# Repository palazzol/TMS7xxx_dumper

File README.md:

# Internal ROM dumper for TMS7xxx series chips

Texas Instruments made a series of chips based on the TMS7000 microprocessor, which can contain internal programs in mask ROM.
General Instrument / Microchip made versions of these chips as well (PIC7000 series).

In addition, at least one commercial IC with a different label is actually one of these internally.
For example, the CTS256A-AL2, which was sold at Radio Shack, is actually a PIC7041.

This design supports all known chips in the series, including:
PIC70XX, TMS70XX, TMS70XXX, TMS77XX, TMS70CXX, and TMS77CXX

This project uses some external code to dump the normally hidden mask ROM, and feed it to a host PC.
In addition, it can identify the type of chip by determining the following parameters:
- RAM size
- ROM size
- Presence of Serial Port
- Process (NMOS or CMOS)

# Instructions:

- Program a 4K 2732-compatible EPROM or FLASH chip with the dumper.bin (Trojan program)
- Program the Arduino Nano with the sketch dumper7k.ino
- Connect via serial terminal, baud rate 115200, 8N1.
- Follow the instructions on screen to identify the chip type and dump any internal rom as a Motorola S-Record format file to the screen
- Save S-Record lines to a .s19 file
- Convert file to binary using srec_cat, or similar tool:

`srec_cat -o <filename>.bin -Binary <filename>.s19`

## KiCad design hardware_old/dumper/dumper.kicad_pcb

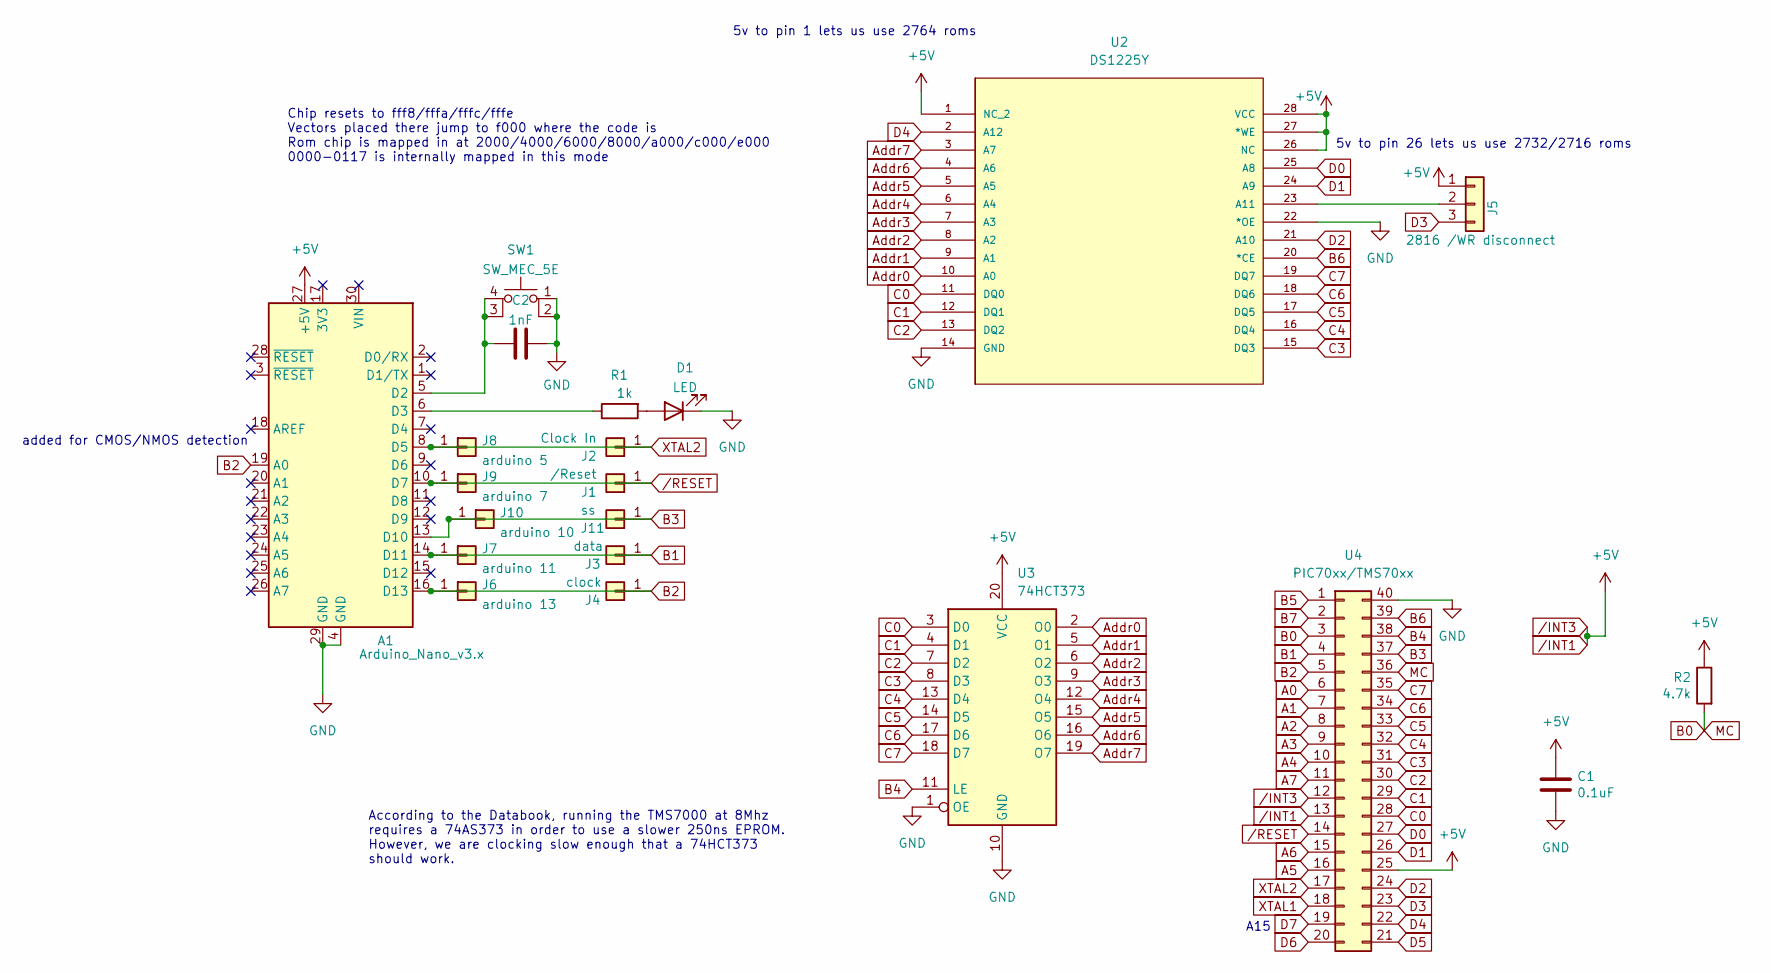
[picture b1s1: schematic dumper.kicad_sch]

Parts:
A1: Arduino_Nano_v3.x; Arduino_Nano
C1: 0.1uF; C_Axial_L3.8mm_D2.6mm_P7.50mm_Horizontal
C2: 1nF; C_Axial_L3.8mm_D2.6mm_P7.50mm_Horizontal
D1: LED; LED_D5.0mm
J1: /Reset; PinHeader_1x01_P2.54mm_Vertical
J2: Clock In; PinHeader_1x01_P2.54mm_Vertical
J3: data; PinHeader_1x01_P2.54mm_Vertical
J4: clock; PinHeader_1x01_P2.54mm_Vertical
J5: 2816 /WR disconnect; PinHeader_1x03_P2.54mm_Vertical
J6: arduino 13; PinHeader_1x01_P2.54mm_Vertical
J7: arduino 11; PinHeader_1x01_P2.54mm_Vertical
J8: arduino 5; PinHeader_1x01_P2.54mm_Vertical
J9: arduino 7; PinHeader_1x01_P2.54mm_Vertical
J10: arduino 10; PinHeader_1x01_P2.54mm_Vertical
J11: ss; PinHeader_1x01_P2.54mm_Vertical
R1: 1k; R_Axial_DIN0207_L6.3mm_D2.5mm_P2.54mm_Vertical
R2: 4.7k; R_Axial_DIN0207_L6.3mm_D2.5mm_P2.54mm_Vertical
SW1: SW_MEC_5E; SW_TH_Tactile_Omron_B3F-10xx
U2: DS1225Y; 21-0245A_28; MANUFACTURER_PART_NUMBER DS1225Y150+
U3: 74HCT373; DIP-20_W7.62mm
U4: PIC70xx/TMS70xx; DIP-40_W15.24mm

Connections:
A0: U4.6
A1: U4.7
A2: U4.8
A3: U4.9
A4: U4.10
A5: U4.16
A6: U4.15
A7: U4.11
Addr0: U2.10 (A0), U3.2 (O0)
Addr1: U2.9 (A1), U3.5 (O1)
Addr2: U2.8 (A2), U3.6 (O2)
Addr3: U2.7 (A3), U3.9 (O3)
Addr4: U2.6 (A4), U3.12 (O4)
Addr5: U2.5 (A5), U3.15 (O5)
Addr6: U2.4 (A6), U3.16 (O6)
Addr7: U2.3 (A7), U3.19 (O7)
B0: R2.2, U4.3, U4.36
B1: A1.14 (D11), J3.1, J7.1, U4.4
B2: A1.16 (D13), A1.19 (A0), J4.1, J6.1, U4.5
B3: A1.13 (D10), J10.1, J11.1, U4.37
B4: U3.11 (LE), U4.38
B5: U4.1
B6: U2.20 (*CE), U4.39
B7: U4.2
C0: U2.11 (DQ0), U3.3 (D0), U4.28
C1: U2.12 (DQ1), U3.4 (D1), U4.29
C2: U2.13 (DQ2), U3.7 (D2), U4.30
C3: U2.15 (DQ3), U3.8 (D3), U4.31
C4: U2.16 (DQ4), U3.13 (D4), U4.32
C5: U2.17 (DQ5), U3.14 (D5), U4.33
C6: U2.18 (DQ6), U3.17 (D6), U4.34
C7: U2.19 (DQ7), U3.18 (D7), U4.35
D0: U2.25 (A8), U4.27
D1: U2.24 (A9), U4.26
D2: U2.21 (A10), U4.24
D3: J5.3, U4.23
D4: U2.2 (A12), U4.22
D5: U4.21
D6: U4.20
D7: U4.19
GND: A1.4 (GND), A1.29 (GND), C1.2, C2.1, D1.1 (K), SW1.1, SW1.2, U2.14 (GND), U2.22 (*OE), U3.1 (OE), U3.10 (GND), U4.40
unnamed: A1.5 (D2), C2.2, SW1.3 (K), SW1.4 (A)
unnamed: A1.6 (D3), R1.1
unnamed: D1.2 (A), R1.2
unnamed: J5.2, U2.23 (A11)
XTAL1: U4.18
XTAL2: A1.8 (D5), J2.1, J8.1, U4.17
/INT1: A1.27 (+5V), C1.1, J5.1, R2.1, U2.1 (NC_2), U2.26 (NC), U2.27 (*WE), U2.28 (VCC), U3.20 (VCC), U4.12, U4.13, U4.25
/RESET: A1.10 (D7), J1.1, J9.1, U4.14

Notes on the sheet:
According to the Databook, running the TMS7000 at 8Mhz requires a 74AS373 in order to use a slower 250ns EPROM. However, we are clocking slow enough that a 74HCT373 should work.
added for CMOS/NMOS detection
5v to pin 26 lets us use 2732/2716 roms
5v to pin 1 lets us use 2764 roms
Chip resets to fff8/fffa/fffc/fffe Vectors placed there jump to f000 where the code is Rom chip is mapped in at 2000/4000/6000/8000/a000/c000/e000 0000-0117 is internally mapped in this mode
A15

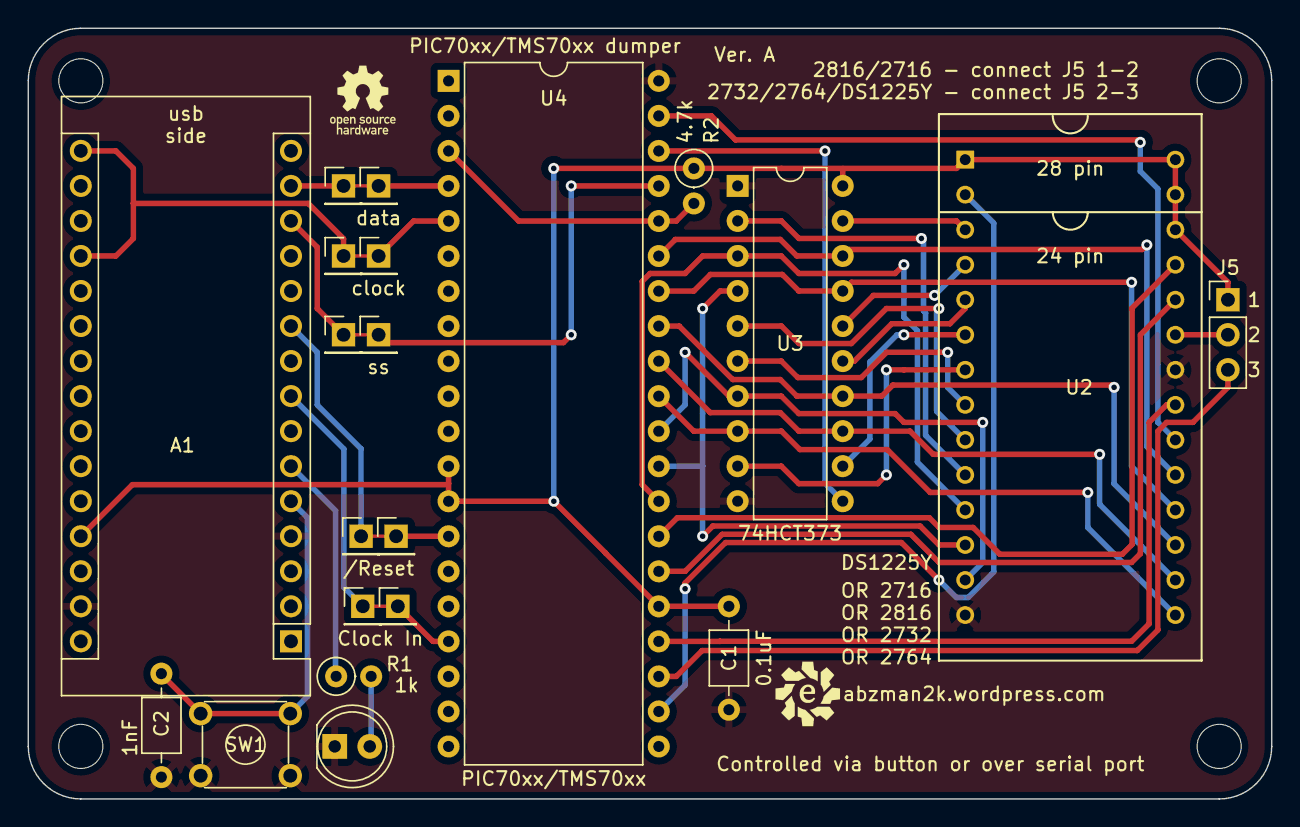
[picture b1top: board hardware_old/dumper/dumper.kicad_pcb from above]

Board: 2 copper layers, 90.2 x 55.9 mm, 21 parts (0 on the bottom side), 35 nets.

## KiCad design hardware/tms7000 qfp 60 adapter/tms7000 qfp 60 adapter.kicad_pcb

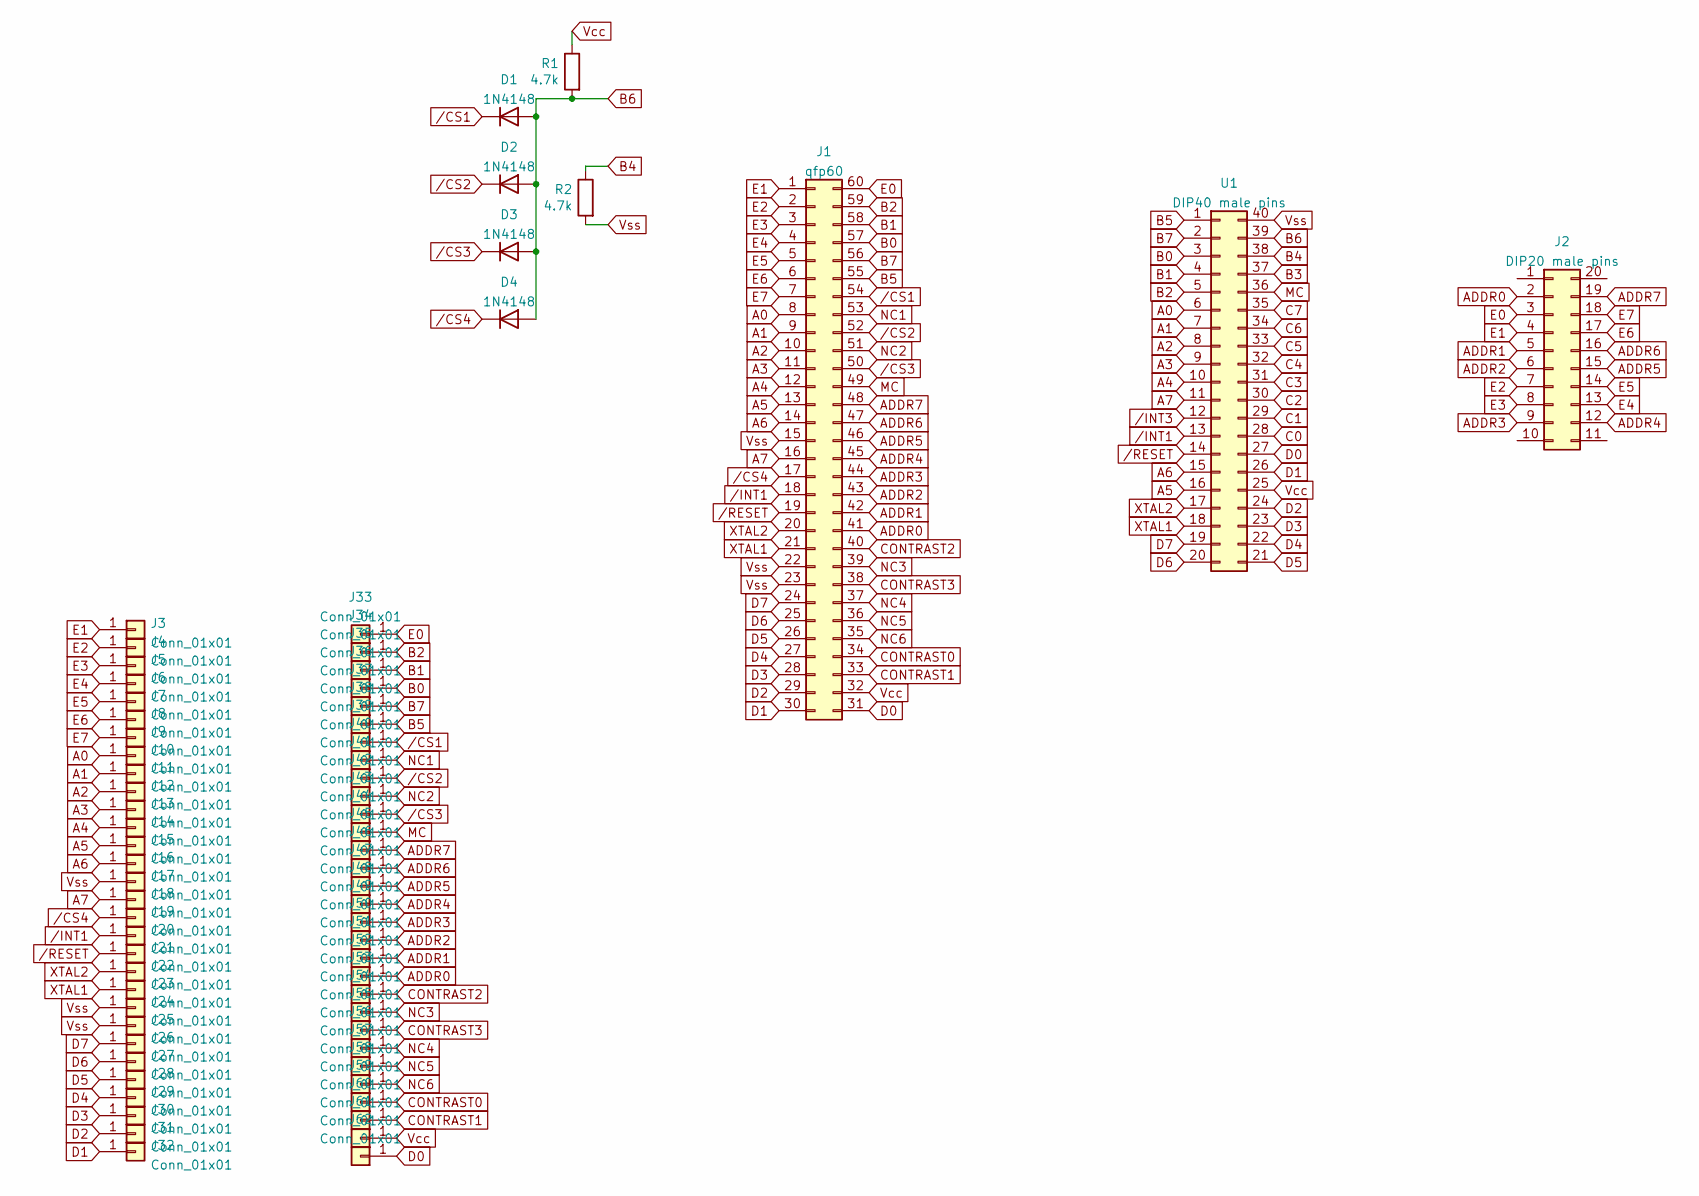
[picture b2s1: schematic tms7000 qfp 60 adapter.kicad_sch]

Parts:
D1, D2, D3, D4: 1N4148; D_DO-35_SOD27_P2.54mm_Vertical_AnodeUp
J1: qfp60; MQFP-60_P0.8mm
J2: DIP20 male pins; DIP-20_W7.62mm
J3, J4, J5, J6, J7, J8, J9, J10, J11, J12, J13, J14, J15, J16, J17, J18, J19, J20, J21, J22, J23, J24, J25, J26, J27, J28, J29, J30, J31, J32, J33, J34, J35, J36, J37, J38, J39, J40, J41, J42, J43, J44, J45, J46, J47, J48, J49, J50, J51, J52, J53, J54, J55, J56, J57, J58, J59, J60, J61, J62: Conn_01x01; PinHeader_1x01_P2.54mm_Vertical
R1, R2: 4.7k; R_Axial_DIN0207_L6.3mm_D2.5mm_P2.54mm_Vertical
U1: DIP40 male pins; DIP-40_W15.24mm

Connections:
A0: J1.8, J10.1, U1.6
A1: J1.9, J11.1, U1.7
A2: J1.10, J12.1, U1.8
A3: J1.11, J13.1, U1.9
A4: J1.12, J14.1, U1.10
A5: J1.13, J15.1, U1.16
A6: J1.14, J16.1, U1.15
A7: J1.16, J18.1, U1.11
ADDR0: J1.41, J2.2, J52.1
ADDR1: J1.42, J2.5, J51.1
ADDR2: J1.43, J2.6, J50.1
ADDR3: J1.44, J2.9, J49.1
ADDR4: J1.45, J2.12, J48.1
ADDR5: J1.46, J2.15, J47.1
ADDR6: J1.47, J2.16, J46.1
ADDR7: J1.48, J2.19, J45.1
B0: J1.57, J36.1, U1.3
B1: J1.58, J35.1, U1.4
B2: J1.59, J34.1, U1.5
B3: U1.37
B4: R2.1, U1.38
B5: J1.55, J38.1, U1.1
B6: D1.2 (A), D2.2 (A), D3.2 (A), D4.2 (A), R1.2, U1.39
B7: J1.56, J37.1, U1.2
C0: U1.28
C1: U1.29
C2: U1.30
C3: U1.31
C4: U1.32
C5: U1.33
C6: U1.34
C7: U1.35
CONTRAST0: J1.34, J59.1
CONTRAST1: J1.33, J60.1
CONTRAST2: J1.40, J53.1
CONTRAST3: J1.38, J55.1
D0: J1.31, J62.1, U1.27
D1: J1.30, J32.1, U1.26
D2: J1.29, J31.1, U1.24
D3: J1.28, J30.1, U1.23
D4: J1.27, J29.1, U1.22
D5: J1.26, J28.1, U1.21
D6: J1.25, J27.1, U1.20
D7: J1.24, J26.1, U1.19
E0: J1.60, J2.3, J33.1
E1: J1.1, J2.4, J3.1
E2: J1.2, J2.7, J4.1
E3: J1.3, J2.8, J5.1
E4: J1.4, J2.13, J6.1
E5: J1.5, J2.14, J7.1
E6: J1.6, J2.17, J8.1
E7: J1.7, J2.18, J9.1
MC: J1.49, J44.1, U1.36
NC1: J1.53, J40.1
NC2: J1.51, J42.1
NC3: J1.39, J54.1
NC4: J1.37, J56.1
NC5: J1.36, J57.1
NC6: J1.35, J58.1
Vcc: J1.32, J61.1, R1.1, U1.25
Vss: J1.15, J1.22, J1.23, J17.1, J24.1, J25.1, R2.2, U1.40
XTAL1: J1.21, J23.1, U1.18
XTAL2: J1.20, J22.1, U1.17
/CS1: D1.1 (K), J1.54, J39.1
/CS2: D2.1 (K), J1.52, J41.1
/CS3: D3.1 (K), J1.50, J43.1
/CS4: D4.1 (K), J1.17, J19.1
/INT1: J1.18, J20.1, U1.13
/INT3: U1.12
/RESET: J1.19, J21.1, U1.14

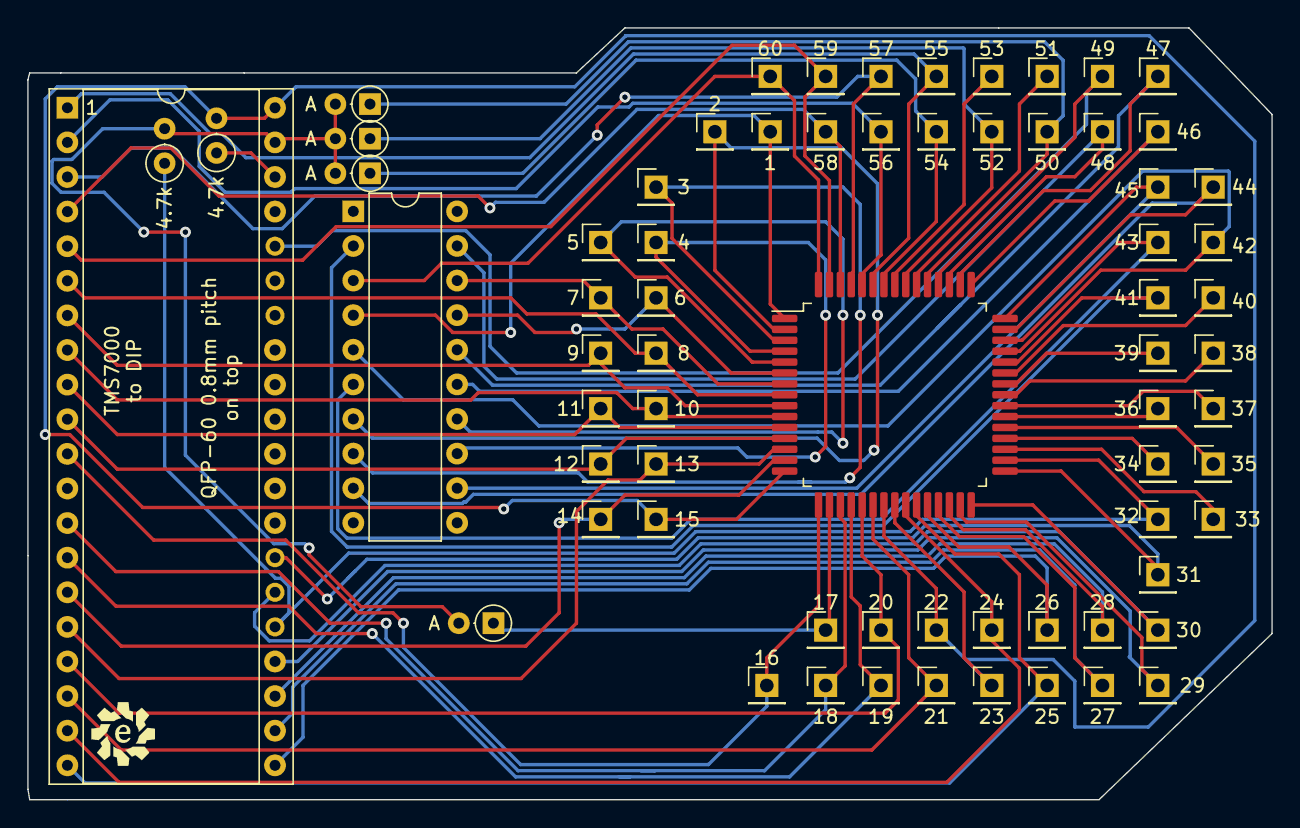
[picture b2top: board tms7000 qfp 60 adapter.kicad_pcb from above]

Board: 2 copper layers, 91.3 x 56.6 mm, 69 parts (0 on the bottom side), 60 nets.

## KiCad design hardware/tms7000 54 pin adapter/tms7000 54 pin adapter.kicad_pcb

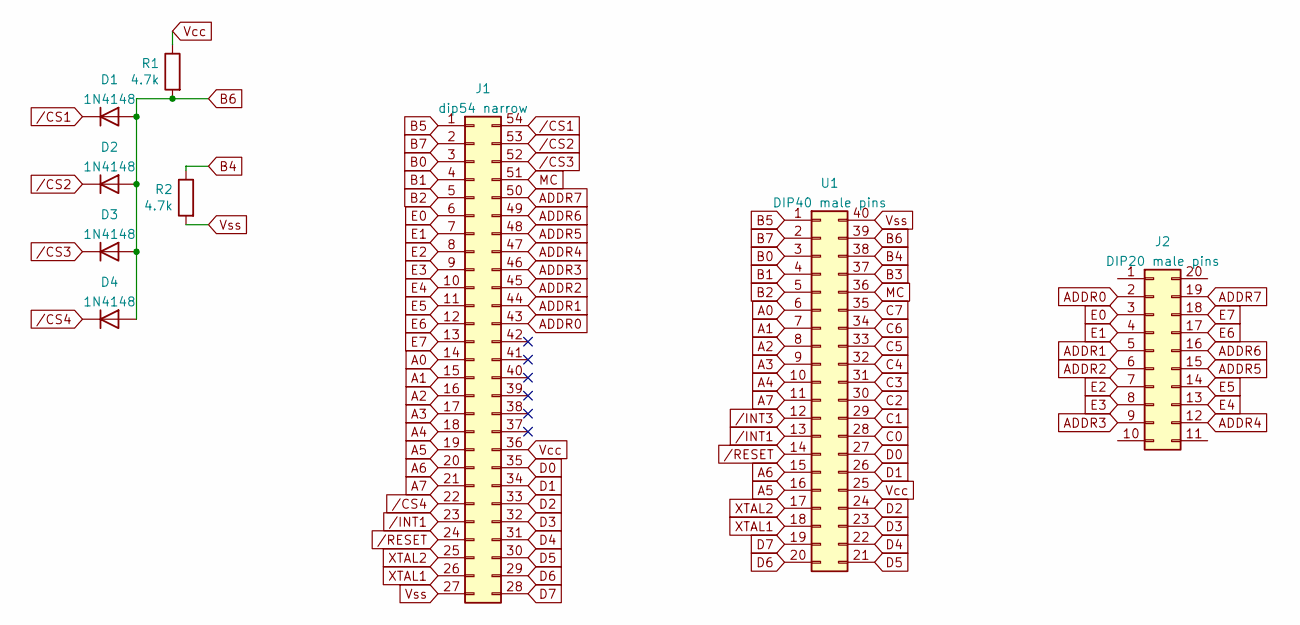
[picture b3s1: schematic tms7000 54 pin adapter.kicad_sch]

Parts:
D1, D2, D3, D4: 1N4148; D_DO-35_SOD27_P2.54mm_Vertical_AnodeUp
J1: dip54 narrow; DIP 54 1.78mm
J2: DIP20 male pins; DIP-20_W7.62mm
R1, R2: 4.7k; R_Axial_DIN0207_L6.3mm_D2.5mm_P2.54mm_Vertical
U1: DIP40 male pins; DIP-40_W15.24mm

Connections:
A0: J1.14, U1.6
A1: J1.15, U1.7
A2: J1.16, U1.8
A3: J1.17, U1.9
A4: J1.18, U1.10
A5: J1.19, U1.16
A6: J1.20, U1.15
A7: J1.21, U1.11
ADDR0: J1.43, J2.2
ADDR1: J1.44, J2.5
ADDR2: J1.45, J2.6
ADDR3: J1.46, J2.9
ADDR4: J1.47, J2.12
ADDR5: J1.48, J2.15
ADDR6: J1.49, J2.16
ADDR7: J1.50, J2.19
B0: J1.3, U1.3
B1: J1.4, U1.4
B2: J1.5, U1.5
B3: U1.37
B4: R2.1, U1.38
B5: J1.1, U1.1
B6: D1.2 (A), D2.2 (A), D3.2 (A), D4.2 (A), R1.2, U1.39
B7: J1.2, U1.2
C0: U1.28
C1: U1.29
C2: U1.30
C3: U1.31
C4: U1.32
C5: U1.33
C6: U1.34
C7: U1.35
D0: J1.35, U1.27
D1: J1.34, U1.26
D2: J1.33, U1.24
D3: J1.32, U1.23
D4: J1.31, U1.22
D5: J1.30, U1.21
D6: J1.29, U1.20
D7: J1.28, U1.19
E0: J1.6, J2.3
E1: J1.7, J2.4
E2: J1.8, J2.7
E3: J1.9, J2.8
E4: J1.10, J2.13
E5: J1.11, J2.14
E6: J1.12, J2.17
E7: J1.13, J2.18
MC: J1.51, U1.36
Vcc: J1.36, R1.1, U1.25
Vss: J1.27, R2.2, U1.40
XTAL1: J1.26, U1.18
XTAL2: J1.25, U1.17
/CS1: D1.1 (K), J1.54
/CS2: D2.1 (K), J1.53
/CS3: D3.1 (K), J1.52
/CS4: D4.1 (K), J1.22
/INT1: J1.23, U1.13
/INT3: U1.12
/RESET: J1.24, U1.14

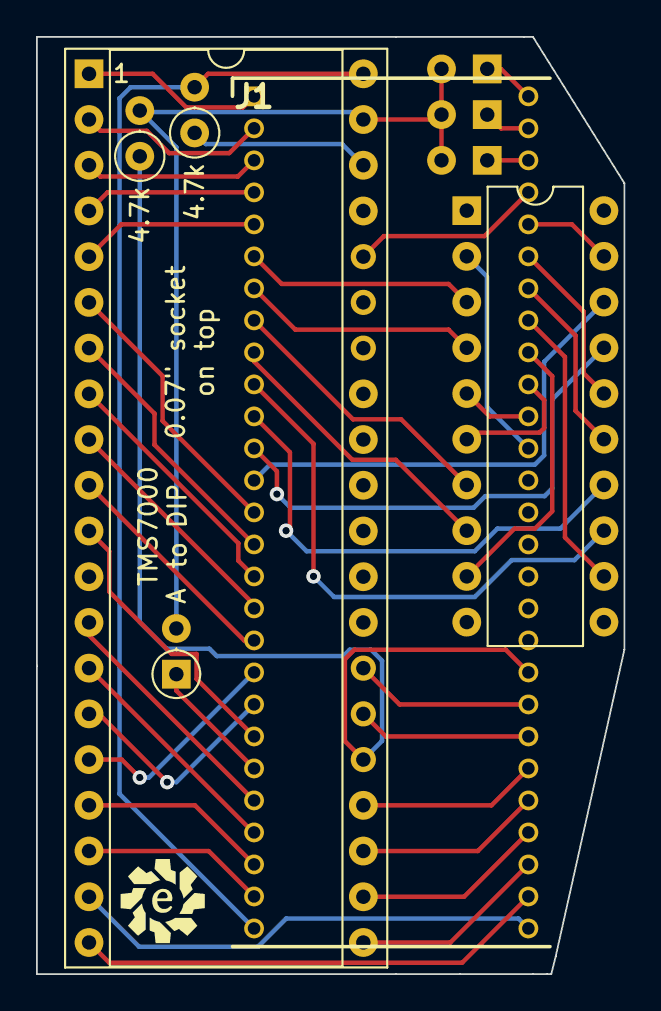
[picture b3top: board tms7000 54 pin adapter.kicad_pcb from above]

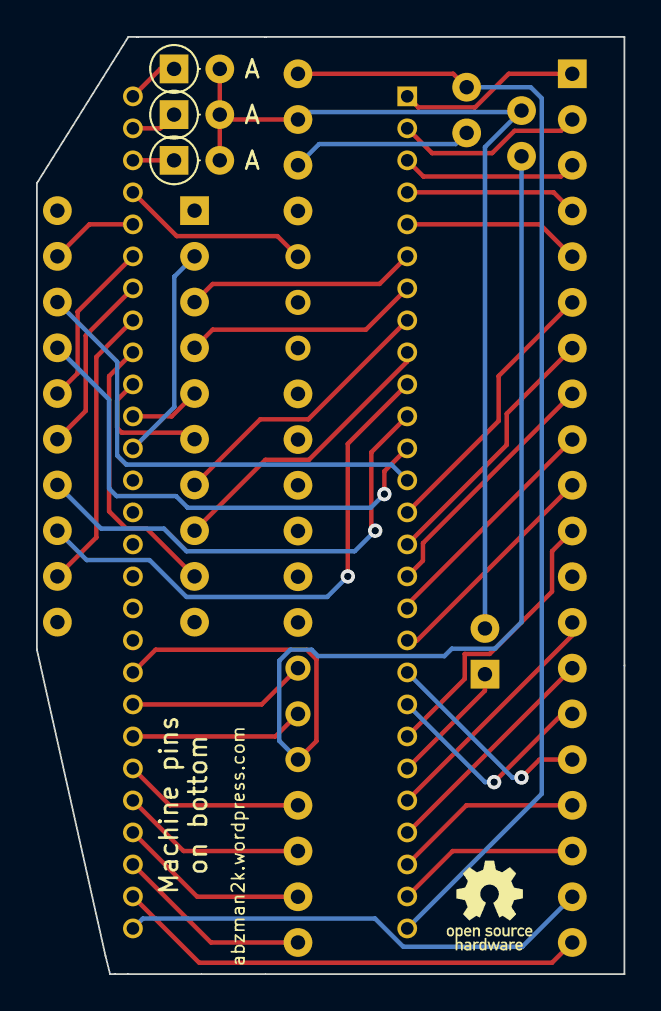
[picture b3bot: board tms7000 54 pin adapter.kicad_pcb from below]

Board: 2 copper layers, 32.6 x 52.1 mm, 9 parts (3 on the bottom side), 50 nets.

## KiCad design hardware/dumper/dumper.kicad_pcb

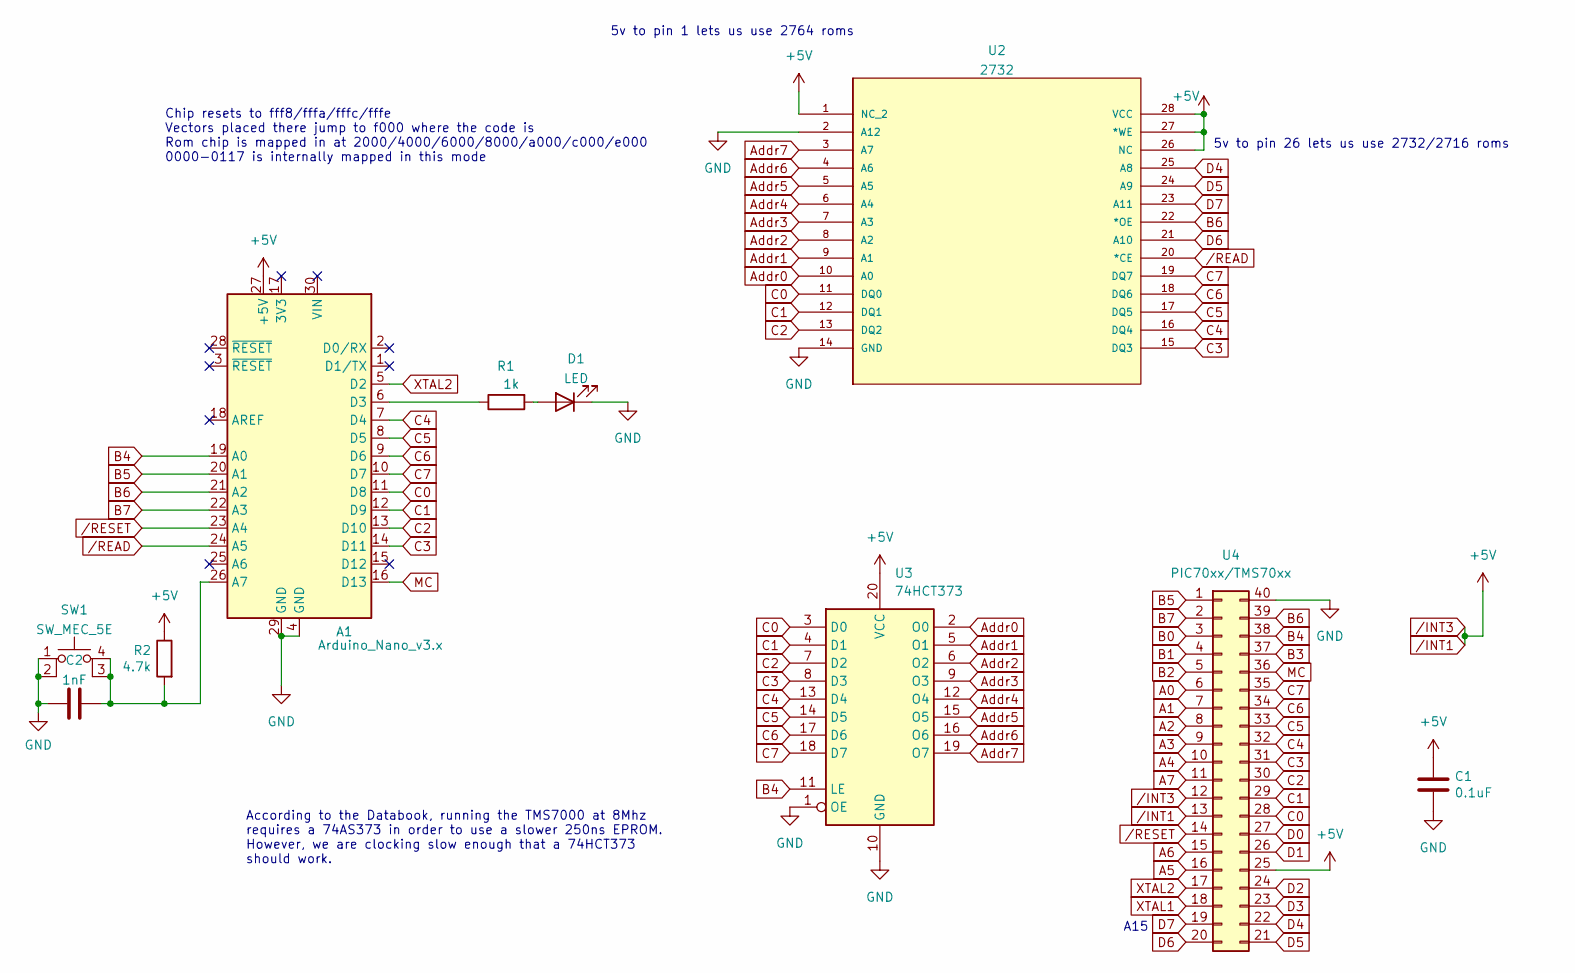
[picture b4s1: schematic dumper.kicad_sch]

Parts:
A1: Arduino_Nano_v3.x; Arduino_Nano
C1: 0.1uF; C_Axial_L3.8mm_D2.6mm_P7.50mm_Horizontal
C2: 1nF; C_Axial_L3.8mm_D2.6mm_P7.50mm_Horizontal
D1: LED; LED_D5.0mm
R1: 1k; R_Axial_DIN0207_L6.3mm_D2.5mm_P2.54mm_Vertical
R2: 4.7k; R_Axial_DIN0207_L6.3mm_D2.5mm_P2.54mm_Vertical
SW1: SW_MEC_5E; SW_TH_Tactile_Omron_B3F-10xx
U2: 2732; 21-0245A_28; MANUFACTURER_PART_NUMBER DS1225Y150+
U3: 74HCT373; DIP-20_W7.62mm
U4: PIC70xx/TMS70xx; DIP-40_W15.24mm

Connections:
A0: U4.6
A1: U4.7
A2: U4.8
A3: U4.9
A4: U4.10
A5: U4.16
A6: U4.15
A7: U4.11
Addr0: U2.10 (A0), U3.2 (O0)
Addr1: U2.9 (A1), U3.5 (O1)
Addr2: U2.8 (A2), U3.6 (O2)
Addr3: U2.7 (A3), U3.9 (O3)
Addr4: U2.6 (A4), U3.12 (O4)
Addr5: U2.5 (A5), U3.15 (O5)
Addr6: U2.4 (A6), U3.16 (O6)
Addr7: U2.3 (A7), U3.19 (O7)
B0: U4.3
B1: U4.4
B2: U4.5
B3: U4.37
B4: A1.19 (A0), U3.11 (LE), U4.38
B5: A1.20 (A1), U4.1
B6: A1.21 (A2), U2.22 (*OE), U4.39
B7: A1.22 (A3), U4.2
C0: A1.11 (D8), U2.11 (DQ0), U3.3 (D0), U4.28
C1: A1.12 (D9), U2.12 (DQ1), U3.4 (D1), U4.29
C2: A1.13 (D10), U2.13 (DQ2), U3.7 (D2), U4.30
C3: A1.14 (D11), U2.15 (DQ3), U3.8 (D3), U4.31
C4: A1.7 (D4), U2.16 (DQ4), U3.13 (D4), U4.32
C5: A1.8 (D5), U2.17 (DQ5), U3.14 (D5), U4.33
C6: A1.9 (D6), U2.18 (DQ6), U3.17 (D6), U4.34
C7: A1.10 (D7), U2.19 (DQ7), U3.18 (D7), U4.35
D0: U4.27
D1: U4.26
D2: U4.24
D3: U4.23
D4: U2.25 (A8), U4.22
D5: U2.24 (A9), U4.21
D6: U2.21 (A10), U4.20
D7: U2.23 (A11), U4.19
GND: A1.4 (GND), A1.29 (GND), C1.2, C2.1, D1.1 (K), SW1.1, SW1.2, U2.2 (A12), U2.14 (GND), U3.1 (OE), U3.10 (GND), U4.40
MC: A1.16 (D13), U4.36
unnamed: A1.6 (D3), R1.1
unnamed: A1.26 (A7), C2.2, R2.2, SW1.3 (K), SW1.4 (A)
unnamed: D1.2 (A), R1.2
XTAL1: U4.18
XTAL2: A1.5 (D2), U4.17
/INT1: A1.27 (+5V), C1.1, R2.1, U2.1 (NC_2), U2.26 (NC), U2.27 (*WE), U2.28 (VCC), U3.20 (VCC), U4.12, U4.13, U4.25
/READ: A1.24 (A5), U2.20 (*CE)
/RESET: A1.23 (A4), U4.14

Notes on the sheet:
According to the Databook, running the TMS7000 at 8Mhz requires a 74AS373 in order to use a slower 250ns EPROM. However, we are clocking slow enough that a 74HCT373 should work.
5v to pin 26 lets us use 2732/2716 roms
5v to pin 1 lets us use 2764 roms
Chip resets to fff8/fffa/fffc/fffe Vectors placed there jump to f000 where the code is Rom chip is mapped in at 2000/4000/6000/8000/a000/c000/e000 0000-0117 is internally mapped in this mode
A15

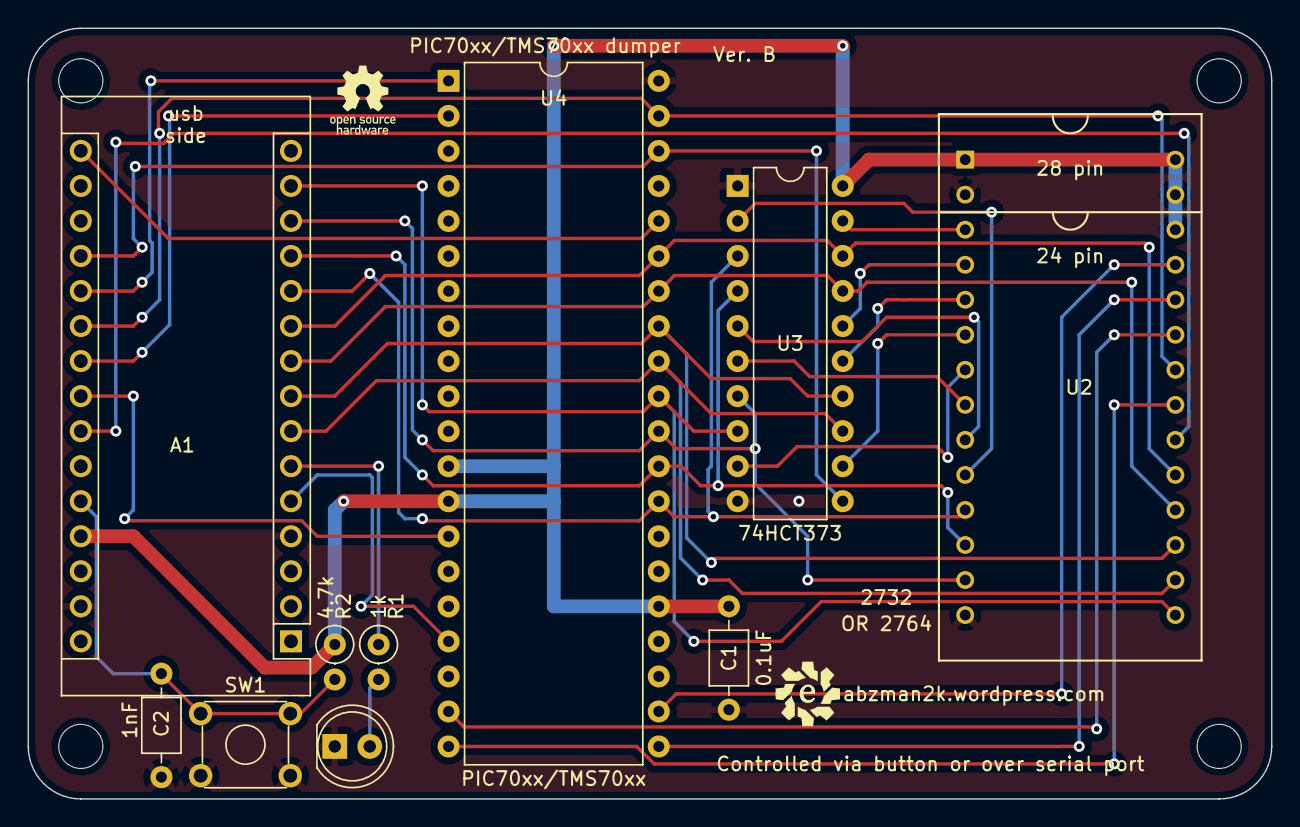
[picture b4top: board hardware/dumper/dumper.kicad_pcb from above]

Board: 2 copper layers, 90.2 x 55.9 mm, 10 parts (0 on the bottom side), 33 nets.

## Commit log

2022-10-15 Add some photos of Original board and some Databook pages
2022-10-16 Add disassembled source and re-commented source
2022-10-16 Move old re code into orig directory
    Update asm file to build with TASM - images match!
2022-10-16 Remove some hardcoded bytes
2022-10-19 added board and tweaked schematic for EPROM variants
2022-10-19 finished initial layout
2022-10-22 Simplified the schematic - no external writes needed
2022-10-22 Add stub for Arduino code
2022-10-22 updated board layout
2022-10-26 Arduino Code:
    Working!
    ASM Code changes:
    Use standard SPI, MSB First, compatible with default Arduino Uno SPI Slave
    Fill byte recommended to be FF
    2K image for 2716, instead of 8K DS1225Y
    Remove broken code to write to DS1225Y
2022-10-29 Fix comments in assembly, Set Baud rate to 115200, Fix Checksum bug
2022-10-29 Move srec2bin.exe and add tasm 3.2 for tms7000 to tools directory
2022-10-30 Add new SRecord Writer class, fixes checksums in output file
2022-11-05 added button and LED, still need software support though
2022-11-20 Added support for new PCB, button, and LED
    Added Chip identification feature, improved user experience
    Fixed bug in byte counter in assembly code
    Add SRecWriter reset() API
2022-11-22 Add Readme, add srec_cat tool
2022-11-27 Fix typo in readme
2022-11-29 Update to full Chip ID, new workflow, added symbol table
2022-12-23 Update dumper firmware to support 12K internal rom (untested)
    Update RAM test algorithm
2022-12-23 Update arduino software to use 0x01 for param instead of S*
    Change ChipID tag to remove problematic slash in filename
2022-12-23 Fix serial port detection on CMOS chips
2022-12-23 Update arduino code to detect NMOS vs CMOS
    Update arduino code to fix overflow issue with 256 bytes of RAM
2022-12-23 Remove specifics about chip numbers - handle on the arduino side
2022-12-23 Fixup some comments
2022-12-23 Handle dumps of 8K and 12K chips
    Streamline nmos/cmos handling
    Using arduino String class now
2022-12-23 Move tab file where asm is, since it seems to need to be there to work
2022-12-23 Add some misc tools which could be useful
2022-12-23 Move/rename Arduino project
2022-12-23 added gerbers
2022-12-23 added version B changes
    silk update and analog sense wire
2022-12-23 added partial databook snippet not on bitsavers
2022-12-23 added more pdf docs
2022-12-24 commented out raw analog read
2022-12-24 auto formatting changes
2022-12-24 fixed resistor value for LED
2022-12-27 added plcc44 adapter
2022-12-27 added 0.7" pitch header adapter
2022-12-31 added gerbers for PLCC and 1.78mm pitch dip adapter
2022-12-31 First cut at changes needed for CT-compatible dumper
    TBD: extra port detection, comments
2022-12-31 Relocate code to E000 (temporary, wont work with chips with >4K of internal ROM)
    Jump to RAM for mode switch, then jump back to external ROM. Seems to work.
    Note: Staying in external ROM during mode switch seems to NOT work.
2022-12-31 Add utility to build 4K image from 256-byte regions
2022-12-31 Update dumper to memory-mapped I/O version
    TBD extra port detection pins
2023-01-01 Cleanup firmware/comments. Add build script. Comment python utility. Update README.md
2023-01-01 Remove need for python program. Generate binary in proper format directly from TASM
2023-01-07 Test version which always dumps C000-FFFF
2023-01-07 Updates for memory-mapped IO
2023-01-09 New dumper works with TMS7000, 70C02, and 70CT40! Needs more testing, process detection not implemented yet
2023-01-10 laid out rev b dumper
    juggled all the address lines and additional arduino wiring to facilitate parallel reads and CT dumping
2023-01-11 added 28 pin adapter
2023-01-11 renamed plcc to plcc44 and added plcc68 adapter
2023-01-14 fixed plcc88, added qfp60, dip54, dip64, and dip64 small pitch
2023-01-28 Fixup bus cycles to work on all variations of chips.
    Skip dumps for now
2023-01-31 added gerbers for all adapters
2023-01-31 added non-parallel rev. A with built in cmos detection
2023-02-02 Ignore dumps dir for now
2023-02-11 Use port F to detect C08 and C48 chips
    Add activity messages to avoid confusion due to startup time
    Fix NMOS/CMOS detection
2023-03-07 added QFP adapter
2024-04-02 Bring in stuff from the main branch under xxx_old, Rev A
2024-04-02 Add all the dumps so far. Lots to sort through here
2024-04-02 Add the old README
2024-04-02 updated qfp64 for fab
2024-04-02 added soic mousebites adapter
2024-04-02 updated for fab
2024-04-06 Consolidate and verify dumps
2024-04-06 Add two more dumps
2024-04-06 Use newer version of romhash.py to generate dumps.txt
2024-04-20 Added new TMS70C08 image from QFP64 chip
2024-04-24 added databook pictures
2024-04-25 opened in kicad 8
